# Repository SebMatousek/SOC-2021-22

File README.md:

# SOC-2021-22
Repozitář pro SOČ Bezdrátově ovládaný roj robotů, zpracovávanou v roce 2021 a 2022.

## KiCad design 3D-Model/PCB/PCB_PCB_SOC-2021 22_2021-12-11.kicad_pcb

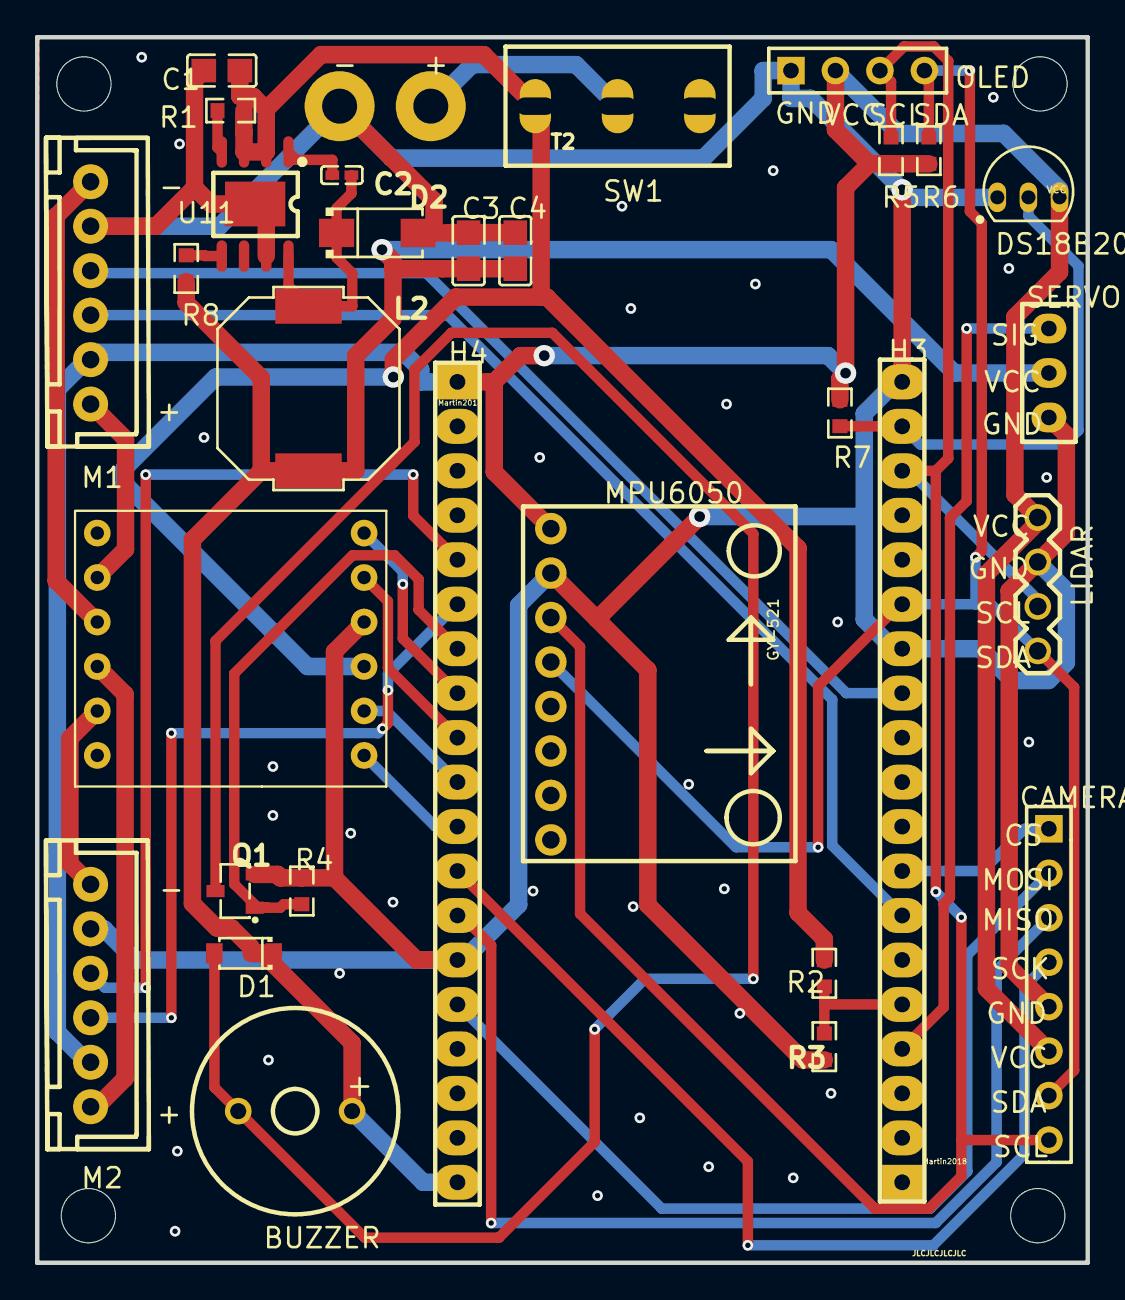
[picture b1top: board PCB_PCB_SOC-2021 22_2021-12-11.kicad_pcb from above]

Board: 2 copper layers, 60.0 x 70.0 mm, 32 parts (0 on the bottom side), 32 nets.

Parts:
+: +; PAD4MM
-: -; PAD4MM
BUZZER: +; BUZZER-12MM
C1, C3, C4: 22uF 16V; C0805
C2: 0.1uF 16V; C0402
CAMERA: ArduCAM-Mini-5MP-Plus; 8PIN
D1: 1N4007W; SOD-123_L2.8-W1.8-LS3.7-RD
D2: B330B-13-F; SOD-106_L4.5-W2.6-LS5.0-RD
DRV8833: DRV8833; DRV8833 DUAL MOTOR DRIVER M
DS18B20: VCC; DS18B20 (TO-92) 3PIN EASY PLANT
H3, H4: Martin2018; HEADER_19
L2: MSS1038-702NLC 6.8uH; MSS1038_MA
LIDAR: LiDAR sensor; PINHEADER1X4N
M1, M2: Encoder motor; XH2.54-6A
MPU6050: GY-521
OLED: 0.91"- OLED-12832; 4PIN
Q1: 2N7002; SC-59-3_L2.9-W1.5-P0.95-LS2.8-BR
R1, R8: 100k; R0603
R2: 470k; R0603
R3: 220k; R0603
R4: 10k; R0603
R5, R6, R7: 4k7; R0603
SERVO: LidarServo; 3_PIN_HEADER
SW1: T2; MTS-102
U11: ADP2302ARDZ-5.0-R7_C76563; SOIC-8_L5.0-W4.0-P1.27-LS6.0-TL-EP

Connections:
+: +.1, SW1.2
+3.3V: CAMERA.6, DS18B20.3, H4.1, LIDAR.1, M1.2, M2.2, MPU6050.1, OLED.2, R5.1, R6.1, R7.1
+5V: BUZZER.+, C3.2, C4.2, D1.1, H4.19, L2.2, R8.2, SERVO.2
BAT+: C1.2, DRV8833.9, R1.1, R2.1, SW1.3, U11.2, U11.3
BATTERYSTATUS: H3.5, R2.2, R3.1
BUZZER: H4.7, Q1.1, R4.2
BUZZER_-: BUZZER.-, D1.2, Q1.3
CS: CAMERA.1, H3.8
ENC1OUTA: H3.7, M1.3
ENC1OUTB: H3.12, M1.4
ENC2OUTA: H4.6, M2.3
ENC2OUTB: H4.5, M2.4
GND: -.1, C1.1, C3.1, C4.1, CAMERA.5, D2.2, DRV8833.10, DS18B20.1, H3.13, H3.19, H4.14, LIDAR.2, M1.5, M2.5, MPU6050.2, OLED.1, Q1.2, R3.2, R4.1, SERVO.3, U11.7, U11.9
IN1: DRV8833.12, H4.8
IN2: DRV8833.11, H4.9
IN3: DRV8833.7, H4.11
IN4: DRV8833.8, H4.10
LIDARSERVO: H3.4, SERVO.1
M1+: DRV8833.2, M1.1
M1-: DRV8833.3, M1.6
M2+: DRV8833.4, M2.1
M2-: DRV8833.5, M2.6
MISO: CAMERA.3, H4.13
MOSI: CAMERA.2, H4.15
SCK: CAMERA.4, H4.12
SCL: CAMERA.8, H3.17, LIDAR.3, MPU6050.3, OLED.3, R5.2
SDA: CAMERA.7, H3.14, LIDAR.4, MPU6050.4, OLED.4, R6.2
TEMP: DS18B20.2, H3.18, R7.2
U11_1: C2.1, U11.1
U11_4: R1.2, U11.4
U11_5: R8.1, U11.5
U11_8: C2.2, D2.1, L2.1, U11.8

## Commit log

2021-06-09 First commit with test.txt file
2021-06-09 ESP BLE Mesh link and prezentation with microcontrollers.
2021-06-16 Create To_Do
2021-06-16 Added TODO xcel file.
2021-06-16 Updated TODO
2021-06-16 Aktualizovane TODO s listy pro každého, nový dokument Napady na napady.
2021-07-13 no message
2021-09-08 push works again, updated changes
2021-10-03 Přidány nákupní košíky a soubor všech součástek a jeijch ceny.
2021-11-06 Nové 3D modely a testovací programy na základní desku.
2021-11-18 Upravené 3D modely. Počátek programu.
2021-11-23 Přidána knihovna na ovládání motorů a knihovna na ovládání enkodérů. Model Karoserie.
2021-12-03 Update pro Dominika
2021-12-03 1. commit
2022-01-02 Made render and lightweight assemblies. Fotos not being commited.
2022-01-02 android app
2022-01-05 Android app started, functioning graphs
2022-01-14 Scrolovní funguje, ale s divnou fyzikou.
2022-01-16 Robot threading not working completely
2022-01-16 Threading works, joystick works. Camera view would interrupt mapping, but ESP32WebServer steals the client for sending and recieving data...
2022-01-18 Robot now able to drive when camera active. For some reason there is a pink-like filter applyed when driving, perhaps low voltage?
2022-01-24 Final version of app; dark mode. Robots on two threads, final code.
2022-02-20 Upravený git, jen potřebné soubory pro sestavení a zprovozění robotů.
2022-11-17 Finální úklid.
